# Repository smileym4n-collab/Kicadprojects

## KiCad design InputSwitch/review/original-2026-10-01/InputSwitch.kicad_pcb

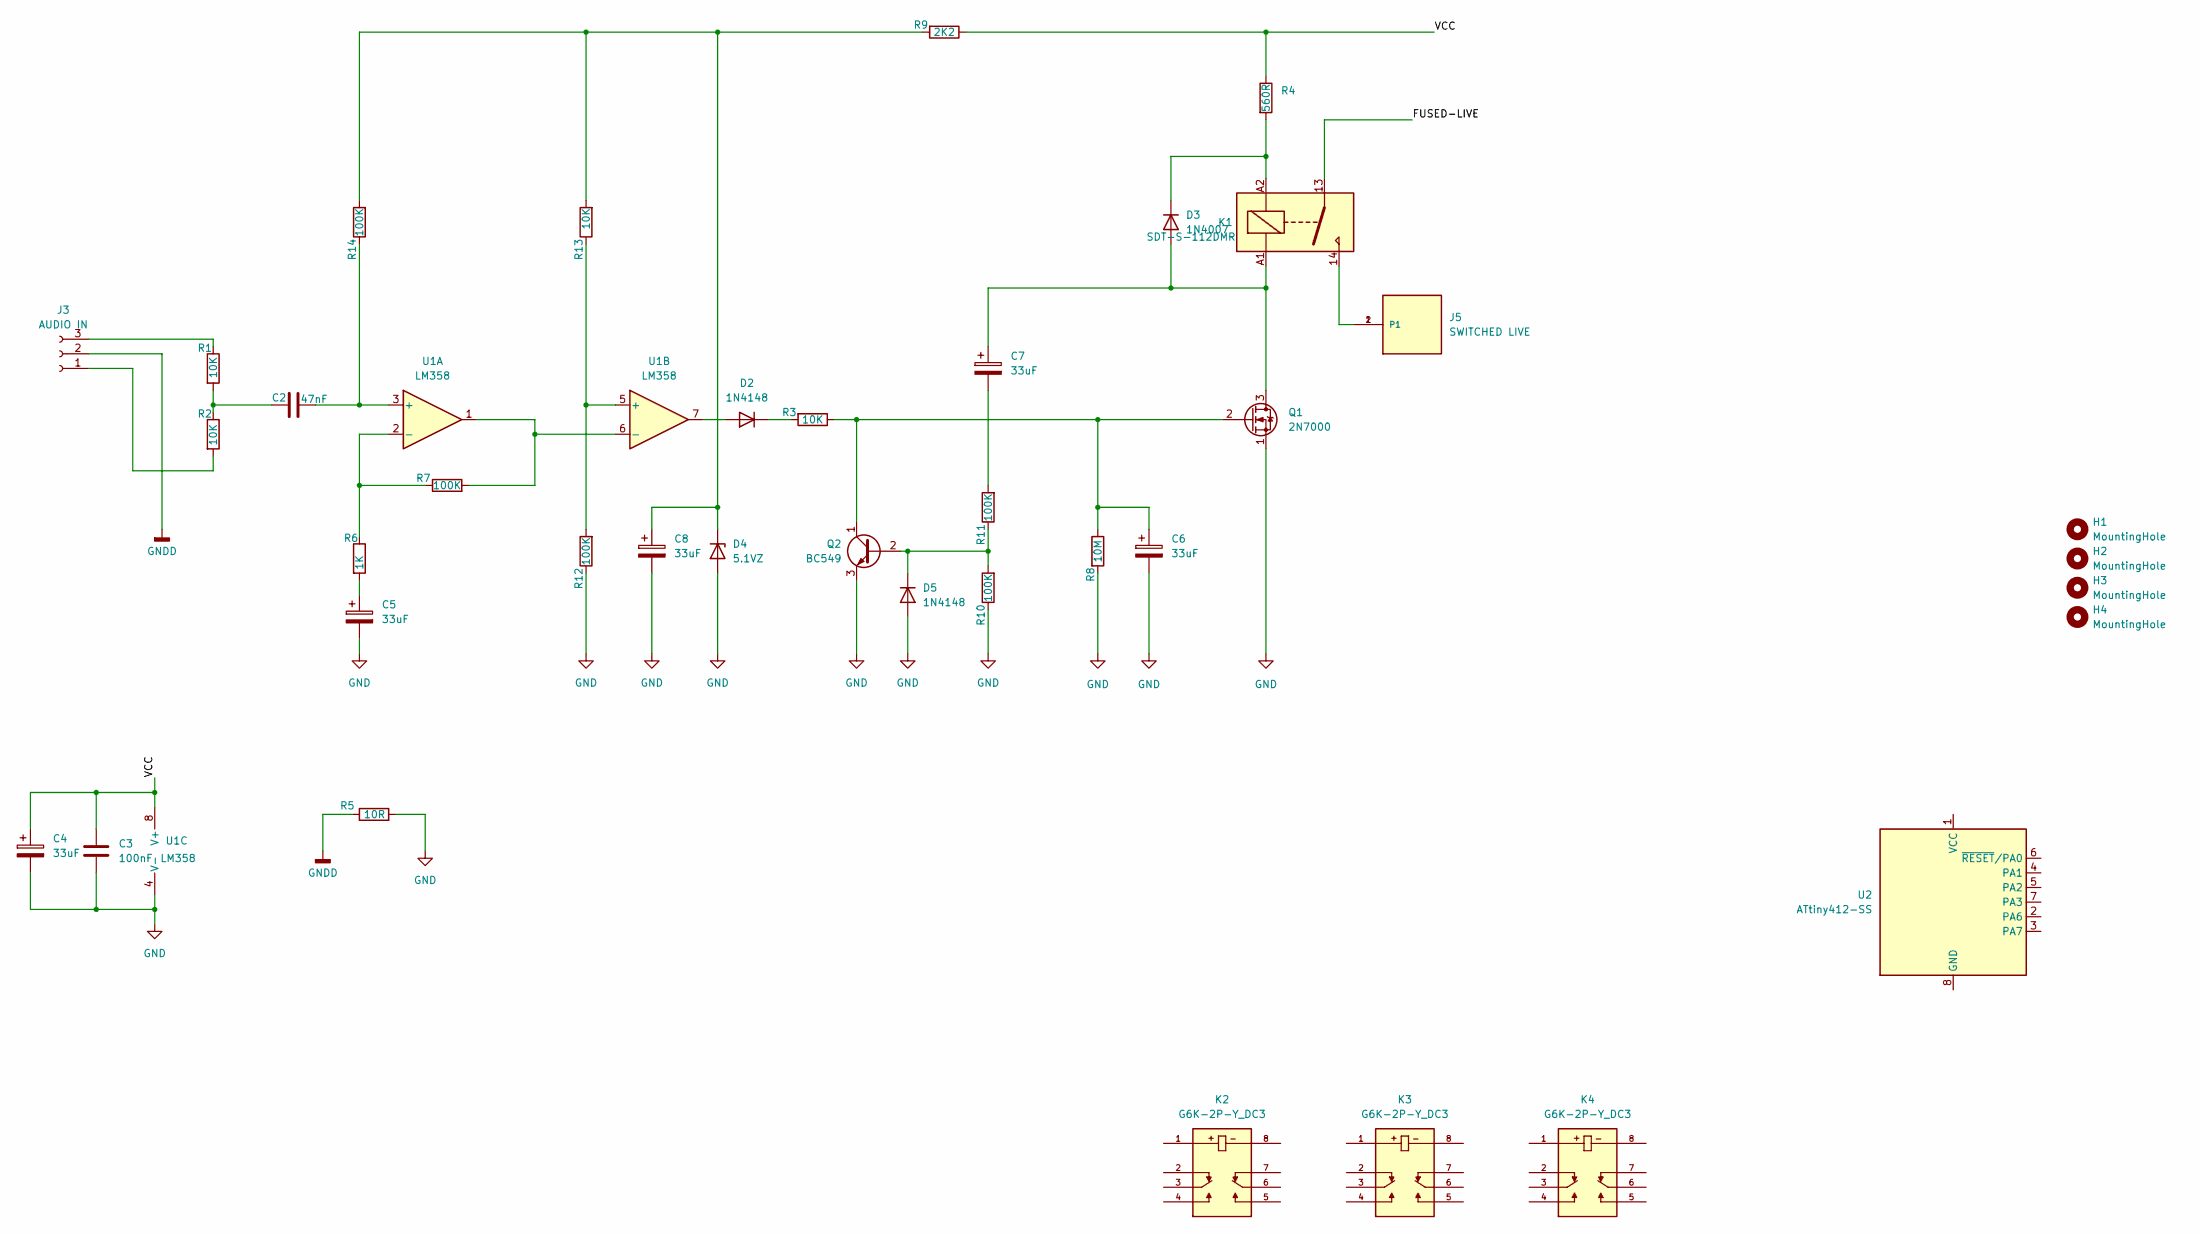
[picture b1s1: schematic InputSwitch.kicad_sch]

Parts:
C2: 47nF; C_Rect_L7.0mm_W2.0mm_P5.00mm
C3: 100nF; C_1206_3216Metric_Pad1.33x1.80mm_HandSolder
C4, C5, C6, C7, C8: 33uF; CP_Radial_D5.0mm_P2.50mm
D2, D5: 1N4148; D_DO-35_SOD27_P7.62mm_Horizontal
D3: 1N4007; D_DO-41_SOD81_P10.16mm_Horizontal
D4: 5.1VZ; D_DO-35_SOD27_P7.62mm_Horizontal
H1, H2, H3, H4: MountingHole; MountingHole_4.3mm_M4
J3: AUDIO IN; JST_XH_B3B-XH-A_1x03_P2.50mm_Vertical
J5: SWITCHED LIVE; TE_62409-1; PART_DESCRIPTION CONN QC TAB 0.250 SOLDER
K1: SDT-S-112DMR; Relay_SPST_Omron_G2RL-1A
K2, K3, K4: G6K-2P-Y_DC3; RELAY_G6K-2P-Y_DC3; PARTREV K106-E1-11
Q1: 2N7000; TO-92L_Inline_Wide
Q2: BC549; TO-92L_Inline_Wide
R1, R2, R3, R13: 10K; R_0805_2012Metric_Pad1.20x1.40mm_HandSolder
R4: 560R; R_Axial_DIN0411_L9.9mm_D3.6mm_P12.70mm_Horizontal
R5: 10R; R_0805_2012Metric_Pad1.20x1.40mm_HandSolder
R6: 1K; R_0805_2012Metric_Pad1.20x1.40mm_HandSolder
R7, R10, R11, R12, R14: 100K; R_0805_2012Metric_Pad1.20x1.40mm_HandSolder
R8: 10M; R_0805_2012Metric_Pad1.20x1.40mm_HandSolder
R9: 2K2; R_0805_2012Metric_Pad1.20x1.40mm_HandSolder
U1: LM358; DIP-8_W7.62mm
U2: ATtiny412-SS; SOIC-8_3.9x4.9mm_P1.27mm

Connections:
/FUSED-LIVE: K1.13
/VCC: C3.1, C4.1, R4.1, R9.1, U1.8 (V+)
GND: C3.2, C4.2, C5.2, C6.2, C8.2, D4.2 (A), D5.2 (A), Q1.1 (S), Q2.3 (E), R5.2, R8.2, R10.1, R12.1, U1.4 (V-)
GNDD: J3.2, R5.1
unnamed: C2.1, R1.2, R2.1
unnamed: C5.1, R6.2
unnamed: C7.2, R11.2
unnamed: D2.2 (A), U1.7
unnamed: D2.1 (K), R3.2
unnamed: C7.1, D3.2 (A), K1.A1, Q1.3 (D)
unnamed: D3.1 (K), K1.A2, R4.2
unnamed: C8.1, D4.1 (K), R9.2, R13.2, R14.2
unnamed: D5.1 (K), Q2.2 (B), R10.2, R11.1
unnamed: J3.1, R2.2
unnamed: J3.3, R1.1
unnamed: J5.1, J5.2 (P1), K1.14
unnamed: C6.1, Q1.2 (G), Q2.1 (C), R3.1, R8.1
unnamed: C2.2, R14.1, U1.3 (+)
unnamed: R6.1, R7.1, U1.2 (-)
unnamed: R12.2, R13.1, U1.5 (+)
unnamed: R7.2, U1.1, U1.6 (-)

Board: 2 copper layers, 42 parts (0 on the bottom side), 20 nets, no tracks yet.

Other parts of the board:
J6: Marantz In; phono
J7: PreAmp in; phono
J8: Out; phono

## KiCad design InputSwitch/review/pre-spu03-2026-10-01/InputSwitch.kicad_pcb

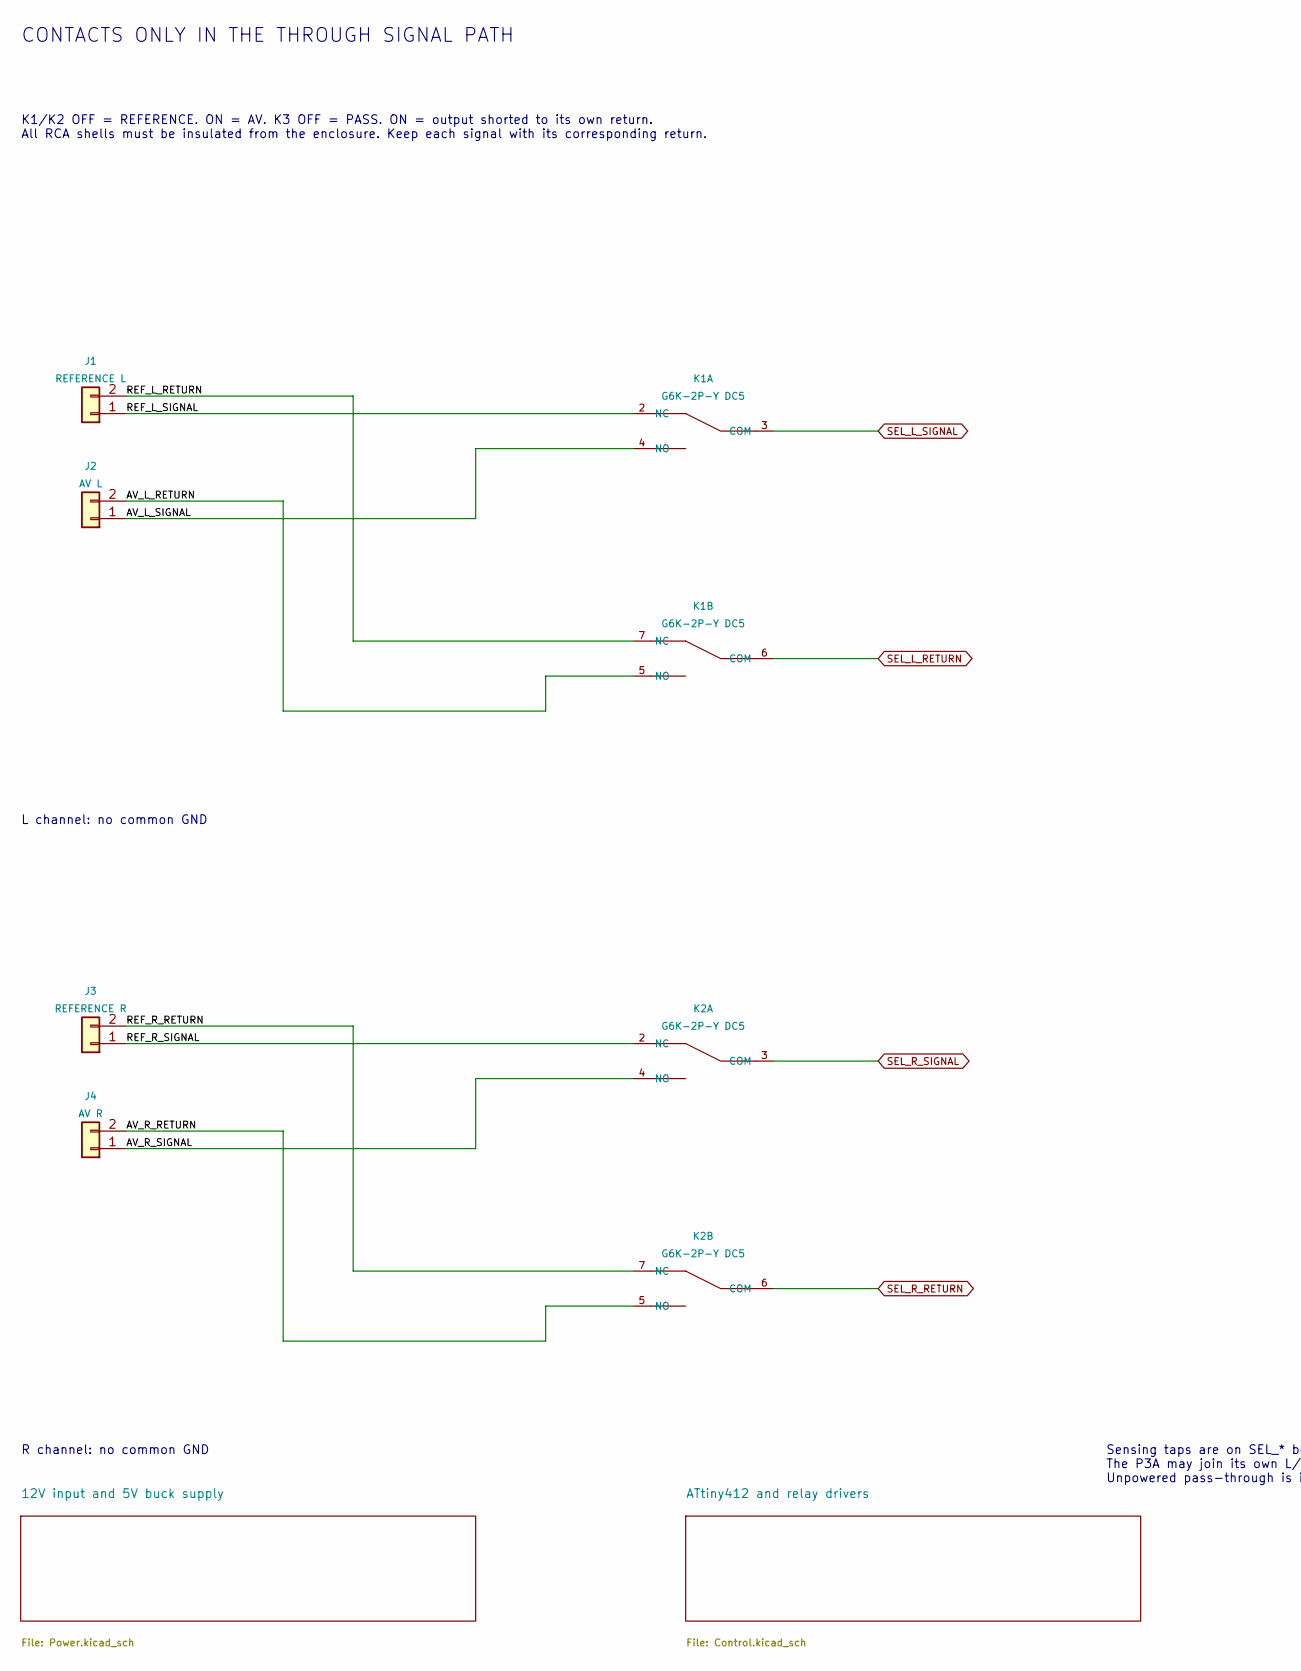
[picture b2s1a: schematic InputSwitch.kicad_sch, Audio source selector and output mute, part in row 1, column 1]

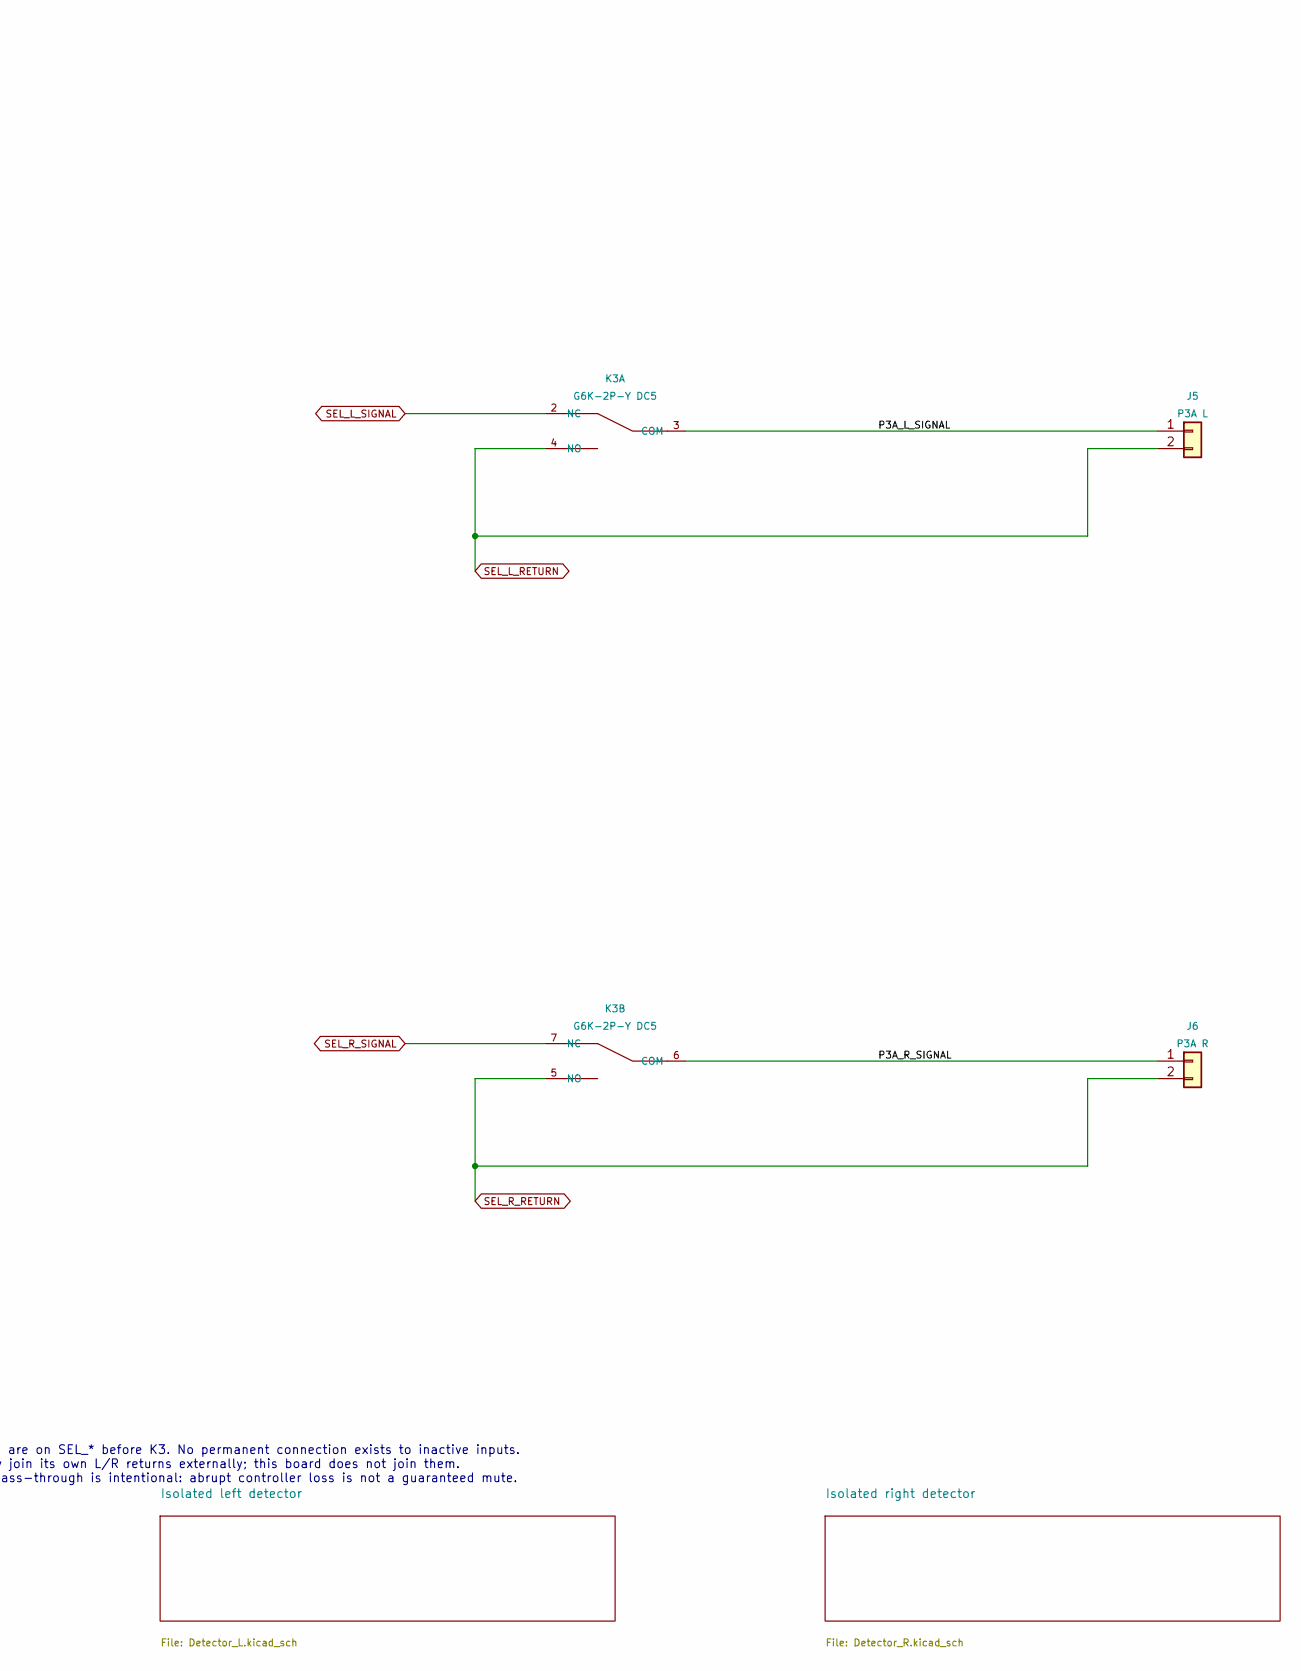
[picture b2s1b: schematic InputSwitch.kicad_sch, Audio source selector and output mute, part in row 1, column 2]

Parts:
J1: REFERENCE L; JST_XH_B2B-XH-A_1x02_P2.50mm_Vertical
J2: AV L; JST_XH_B2B-XH-A_1x02_P2.50mm_Vertical
J3: REFERENCE R; JST_XH_B2B-XH-A_1x02_P2.50mm_Vertical
J4: AV R; JST_XH_B2B-XH-A_1x02_P2.50mm_Vertical
J5: P3A L; JST_XH_B2B-XH-A_1x02_P2.50mm_Vertical
J6: P3A R; JST_XH_B2B-XH-A_1x02_P2.50mm_Vertical
K1, K2, K3: G6K-2P-Y DC5; Relay_DPDT_Omron_G6K-2P-Y

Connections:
/AV_L_RETURN: J2.2, K1.5 (NO)
/AV_L_SIGNAL: J2.1, K1.4 (NO)
/AV_R_RETURN: J4.2, K2.5 (NO)
/AV_R_SIGNAL: J4.1, K2.4 (NO)
/P3A_L_SIGNAL: J5.1, K3.3 (COM)
/P3A_R_SIGNAL: J6.1, K3.6 (COM)
/REF_L_RETURN: J1.2, K1.7 (NC)
/REF_L_SIGNAL: J1.1, K1.2 (NC)
/REF_R_RETURN: J3.2, K2.7 (NC)
/REF_R_SIGNAL: J3.1, K2.2 (NC)
SEL_L_RETURN: J5.2, K1.6 (COM), K3.4 (NO); also elsewhere on the board
SEL_L_SIGNAL: K1.3 (COM), K3.2 (NC); also elsewhere on the board
SEL_R_RETURN: J6.2, K2.6 (COM), K3.5 (NO); also elsewhere on the board
SEL_R_SIGNAL: K2.3 (COM), K3.7 (NC); also elsewhere on the board

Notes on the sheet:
CONTACTS ONLY IN THE THROUGH SIGNAL PATH
K1/K2 OFF = REFERENCE. ON = AV. K3 OFF = PASS. ON = output shorted to its own return. All RCA shells must be insulated from the enclosure. Keep each signal with its corresponding return.
R channel: no common GND
Sensing taps are on SEL_* before K3. No permanent connection exists to inactive inputs. The P3A may join its own L/R returns externally; this board does not join them. Unpowered pass-through is intentional: abrupt controller loss is not a guaranteed mute.
L channel: no common GND

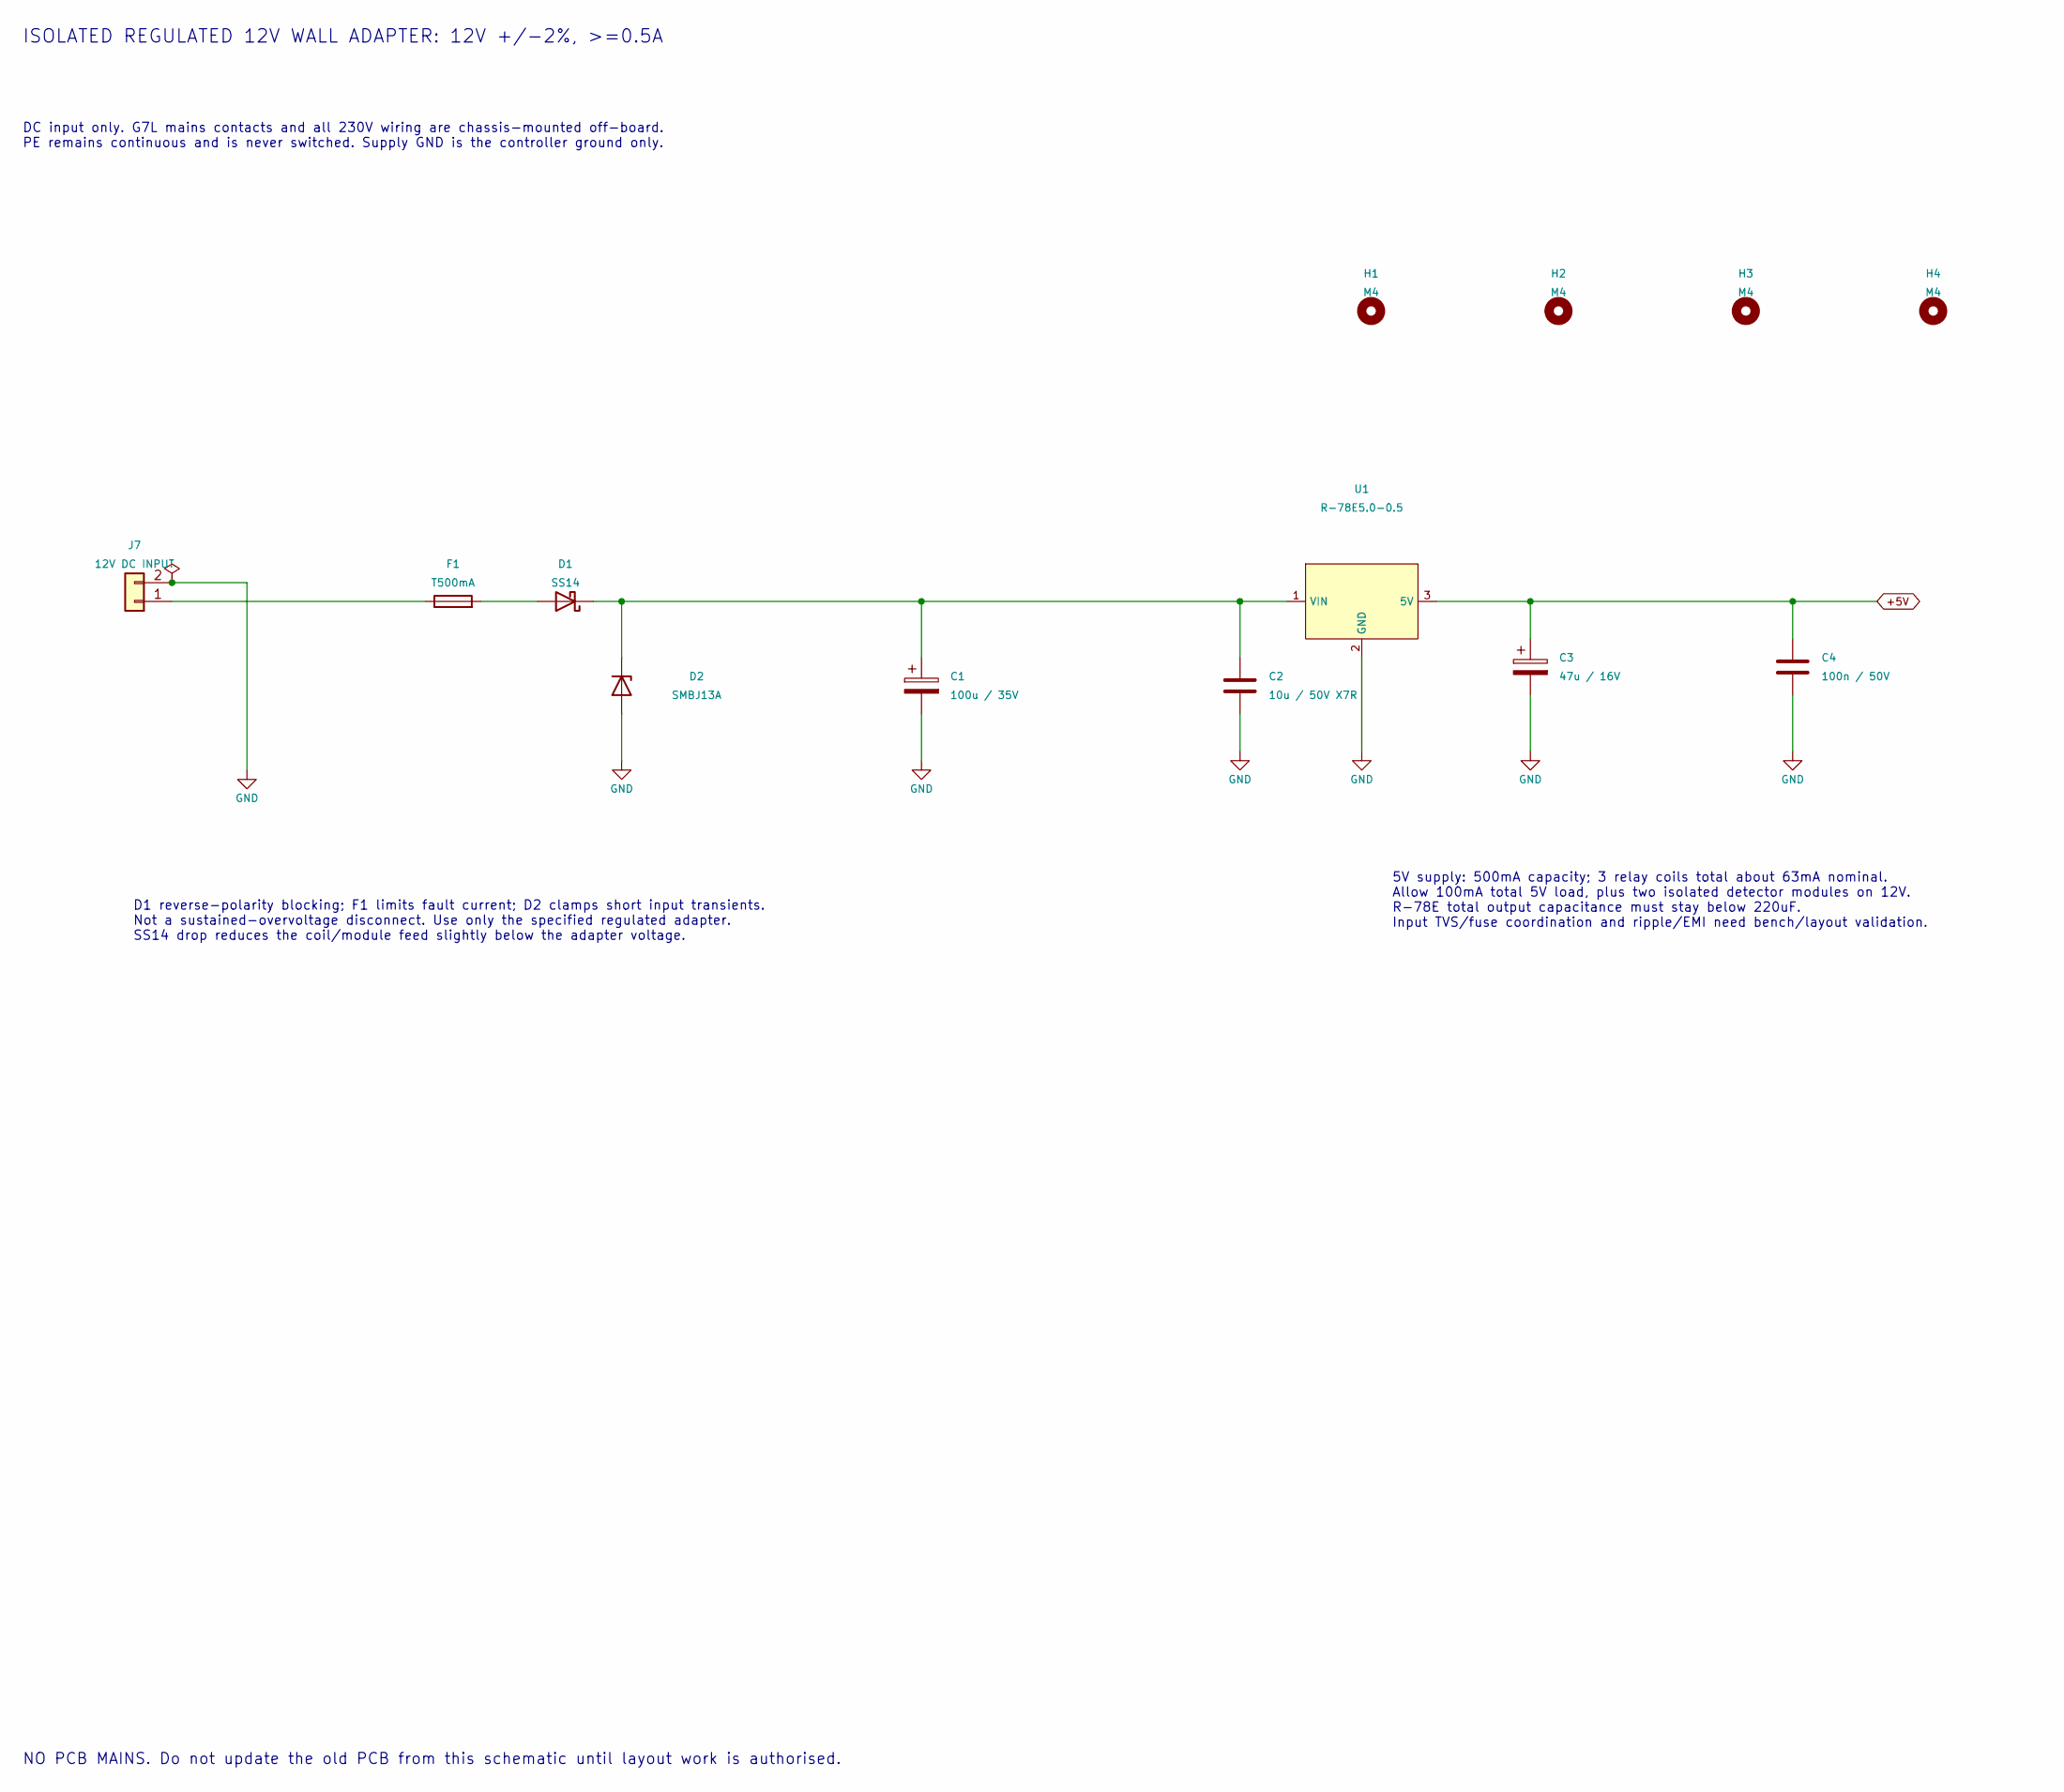
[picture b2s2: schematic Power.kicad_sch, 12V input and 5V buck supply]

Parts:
C1: 100u / 35V; CP_Radial_D6.3mm_P2.50mm
C2: 10u / 50V X7R; C_0805_2012Metric_Pad1.18x1.45mm_HandSolder
C3: 47u / 16V; CP_Radial_D5.0mm_P2.50mm
C4: 100n / 50V; C_0805_2012Metric_Pad1.18x1.45mm_HandSolder
D1: SS14; D_SMA
D2: SMBJ13A; D_SMB
F1: T500mA; Fuseholder_Cylinder-5x20mm_Bulgin_FX0457_Horizontal_Closed
H1, H2, H3, H4: M4; MountingHole_4.3mm_M4
J7: 12V DC INPUT; JST_XH_B2B-XH-A_1x02_P2.50mm_Vertical
U1: R-78E5.0-0.5; Converter_DCDC_RECOM_R-78E-0.5_THT

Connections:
+5V: C3.1, C4.1, U1.3 (5V); also elsewhere on the board
GND: C1.2, C2.2, C3.2, C4.2, D2.2 (A), J7.2, U1.2 (GND); also elsewhere on the board
unnamed: D1.2 (A), F1.2
unnamed: F1.1, J7.1

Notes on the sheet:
ISOLATED REGULATED 12V WALL ADAPTER: 12V +/-2%, >=0.5A
NO PCB MAINS. Do not update the old PCB from this schematic until layout work is authorised.
5V supply: 500mA capacity; 3 relay coils total about 63mA nominal. Allow 100mA total 5V load, plus two isolated detector modules on 12V. R-78E total output capacitance must stay below 220uF. Input TVS/fuse coordination and ripple/EMI need bench/layout validation.
DC input only. G7L mains contacts and all 230V wiring are chassis-mounted off-board. PE remains continuous and is never switched. Supply GND is the controller ground only.
D1 reverse-polarity blocking; F1 limits fault current; D2 clamps short input transients. Not a sustained-overvoltage disconnect. Use only the specified regulated adapter. SS14 drop reduces the coil/module feed slightly below the adapter voltage.

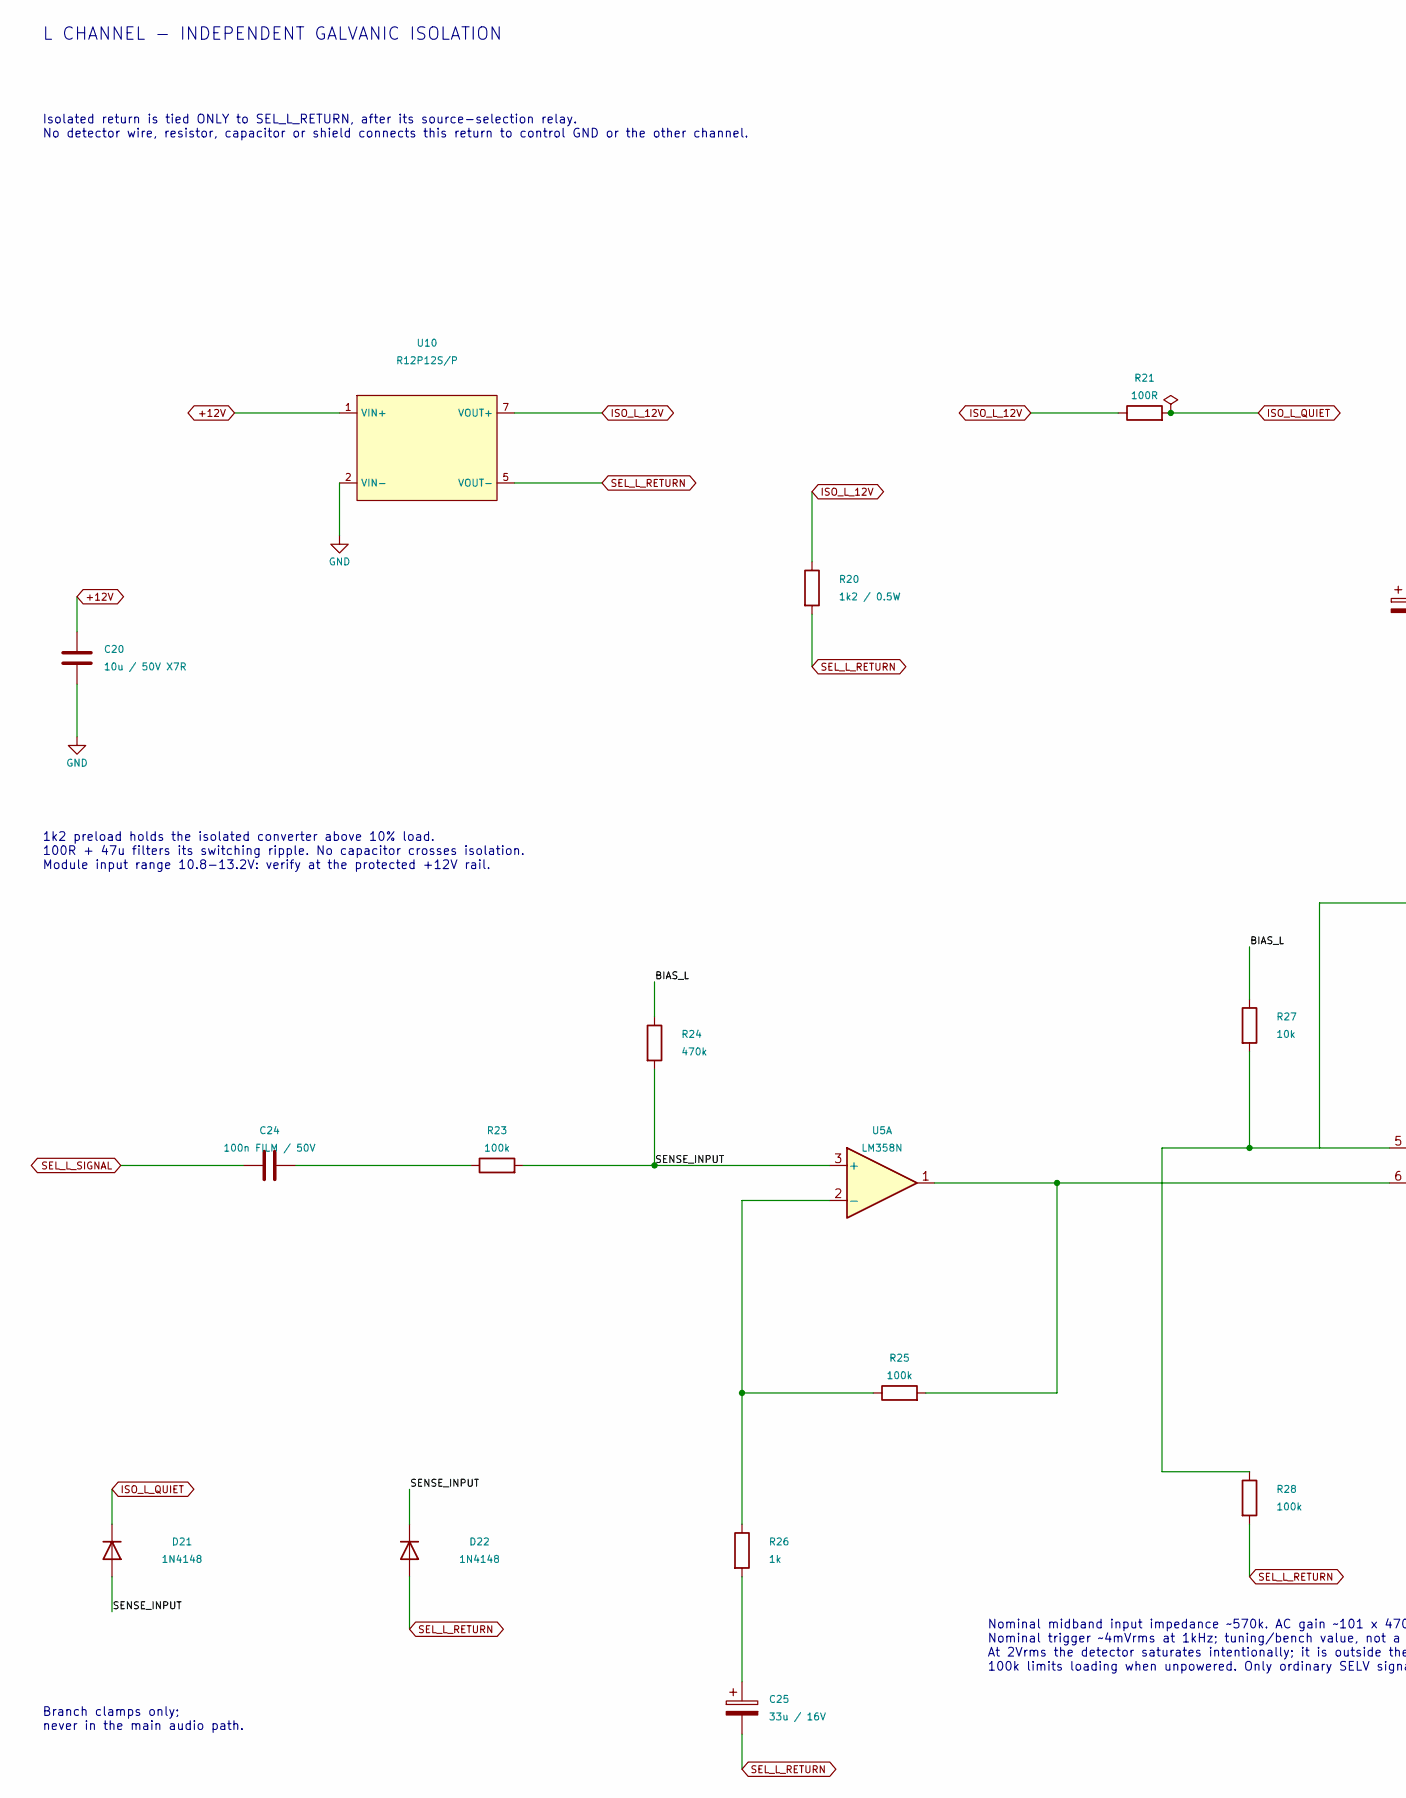
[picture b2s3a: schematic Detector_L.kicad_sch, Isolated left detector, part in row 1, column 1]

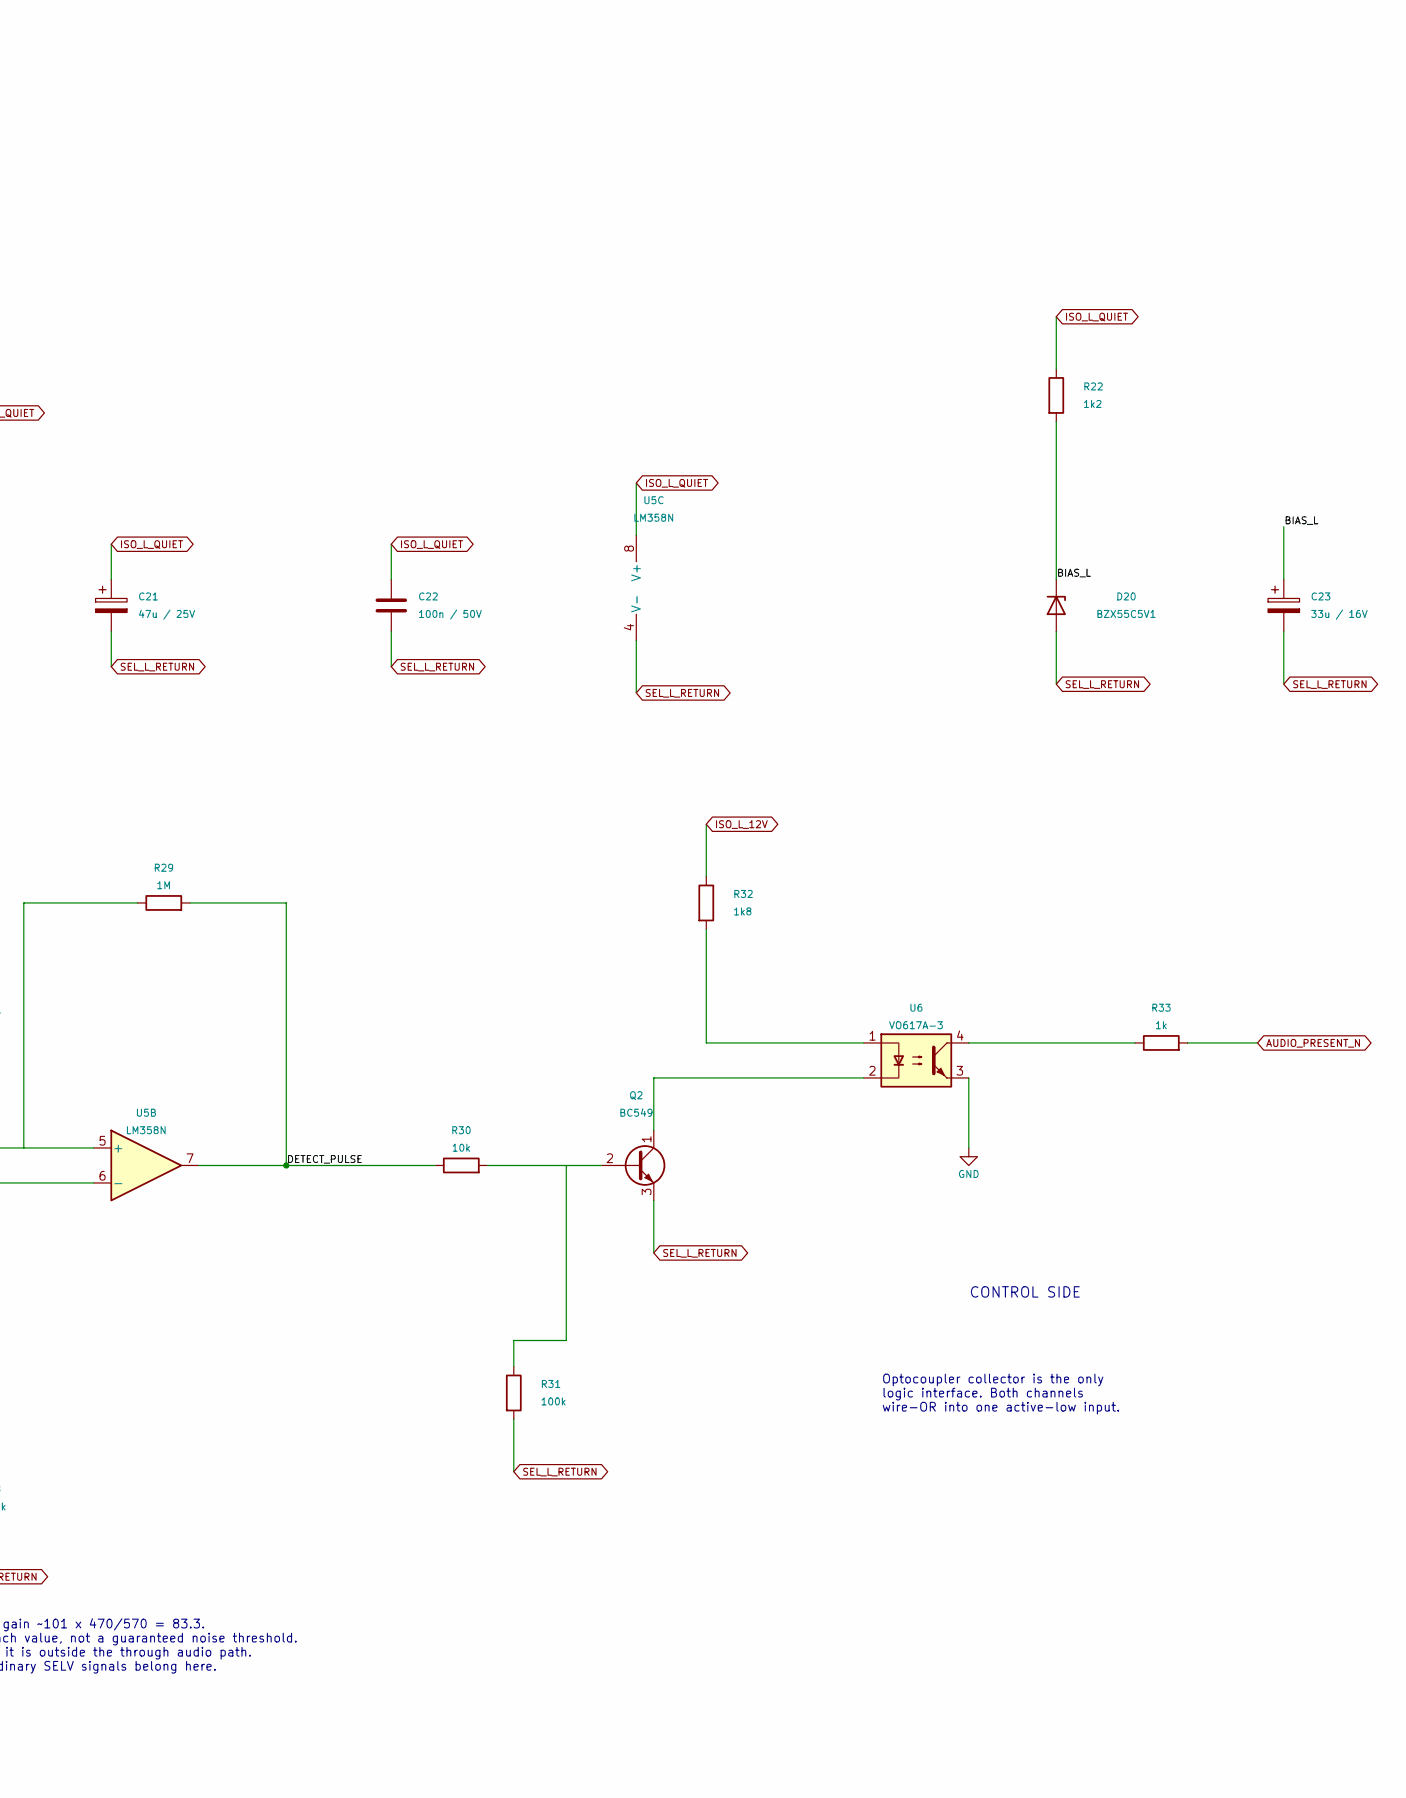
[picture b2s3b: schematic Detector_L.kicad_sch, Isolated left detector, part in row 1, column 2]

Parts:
C20: 10u / 50V X7R; C_0805_2012Metric_Pad1.18x1.45mm_HandSolder
C21: 47u / 25V; CP_Radial_D5.0mm_P2.50mm
C22: 100n / 50V; C_0805_2012Metric_Pad1.18x1.45mm_HandSolder
C23, C25: 33u / 16V; CP_Radial_D5.0mm_P2.50mm
C24: 100n FILM / 50V; C_Rect_L7.0mm_W2.0mm_P5.00mm
D20: BZX55C5V1; D_DO-35_SOD27_P7.62mm_Horizontal
D21, D22: 1N4148; D_DO-35_SOD27_P7.62mm_Horizontal
Q2: BC549; TO-92_Inline
R20: 1k2 / 0.5W; R_Axial_DIN0207_L6.3mm_D2.5mm_P10.16mm_Horizontal
R21: 100R; R_0805_2012Metric_Pad1.20x1.40mm_HandSolder
R22: 1k2; R_0805_2012Metric_Pad1.20x1.40mm_HandSolder
R23, R25, R28, R31: 100k; R_0805_2012Metric_Pad1.20x1.40mm_HandSolder
R24: 470k; R_0805_2012Metric_Pad1.20x1.40mm_HandSolder
R26, R33: 1k; R_0805_2012Metric_Pad1.20x1.40mm_HandSolder
R27, R30: 10k; R_0805_2012Metric_Pad1.20x1.40mm_HandSolder
R29: 1M; R_0805_2012Metric_Pad1.20x1.40mm_HandSolder
R32: 1k8; R_0805_2012Metric_Pad1.20x1.40mm_HandSolder
U5: LM358N; DIP-8_W7.62mm
U6: VO617A-3; DIP-4_W7.62mm
U10: R12P12S/P; R12P12S_P_SIP7

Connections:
/Isolated left detector/BIAS_L: C23.1, D20.1 (K), R22.2, R24.1, R27.1
/Isolated left detector/DETECT_PULSE: R29.2, R30.1, U5.7
/Isolated left detector/SENSE_INPUT: D21.2 (A), D22.1 (K), R23.2, R24.2, U5.3 (+)
AUDIO_PRESENT_N: R33.2; also elsewhere on the board
GND: C20.2, U6.3, U10.2 (VIN-); also elsewhere on the board
ISO_L_12V: R20.1, R21.1, R32.1, U10.7 (VOUT+)
ISO_L_QUIET: C21.1, C22.1, D21.1 (K), R21.2, R22.1, U5.8 (V+)
unnamed: C24.2, R23.1
unnamed: C25.1, R26.2
unnamed: Q2.2 (B), R30.2
unnamed: Q2.1 (C), U6.2
unnamed: R32.2, U6.1
unnamed: R33.1, U6.4
unnamed: R25.1, R26.1, U5.2 (-)
unnamed: R27.2, R28.1, U5.5 (+)
unnamed: R25.2, U5.1, U5.6 (-)
SEL_L_RETURN: C21.2, C22.2, C23.2, C25.2, D20.2 (A), D22.2 (A), Q2.3 (E), R20.2, R28.2, R31.2, U5.4 (V-), U10.5 (VOUT-); also elsewhere on the board
SEL_L_SIGNAL: C24.1; also elsewhere on the board

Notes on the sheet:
1k2 preload holds the isolated converter above 10% load. 100R + 47u filters its switching ripple. No capacitor crosses isolation. Module input range 10.8-13.2V: verify at the protected +12V rail.
Nominal midband input impedance ~570k. AC gain ~101 x 470/570 = 83.3. Nominal trigger ~4mVrms at 1kHz; tuning/bench value, not a guaranteed noise threshold. At 2Vrms the detector saturates intentionally; it is outside the through audio path. 100k limits loading when unpowered. Only ordinary SELV si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
Optocoupler collector is the only logic interface. Both channels wire-OR into one active-low input.
L CHANNEL - INDEPENDENT GALVANIC ISOLATION
Branch clamps only; never in the main audio path.
CONTROL SIDE
Isolated return is tied ONLY to SEL_L_RETURN, after its source-selection relay. No detector wire, resistor, capacitor or shield connects this return to control GND or the other channel.
